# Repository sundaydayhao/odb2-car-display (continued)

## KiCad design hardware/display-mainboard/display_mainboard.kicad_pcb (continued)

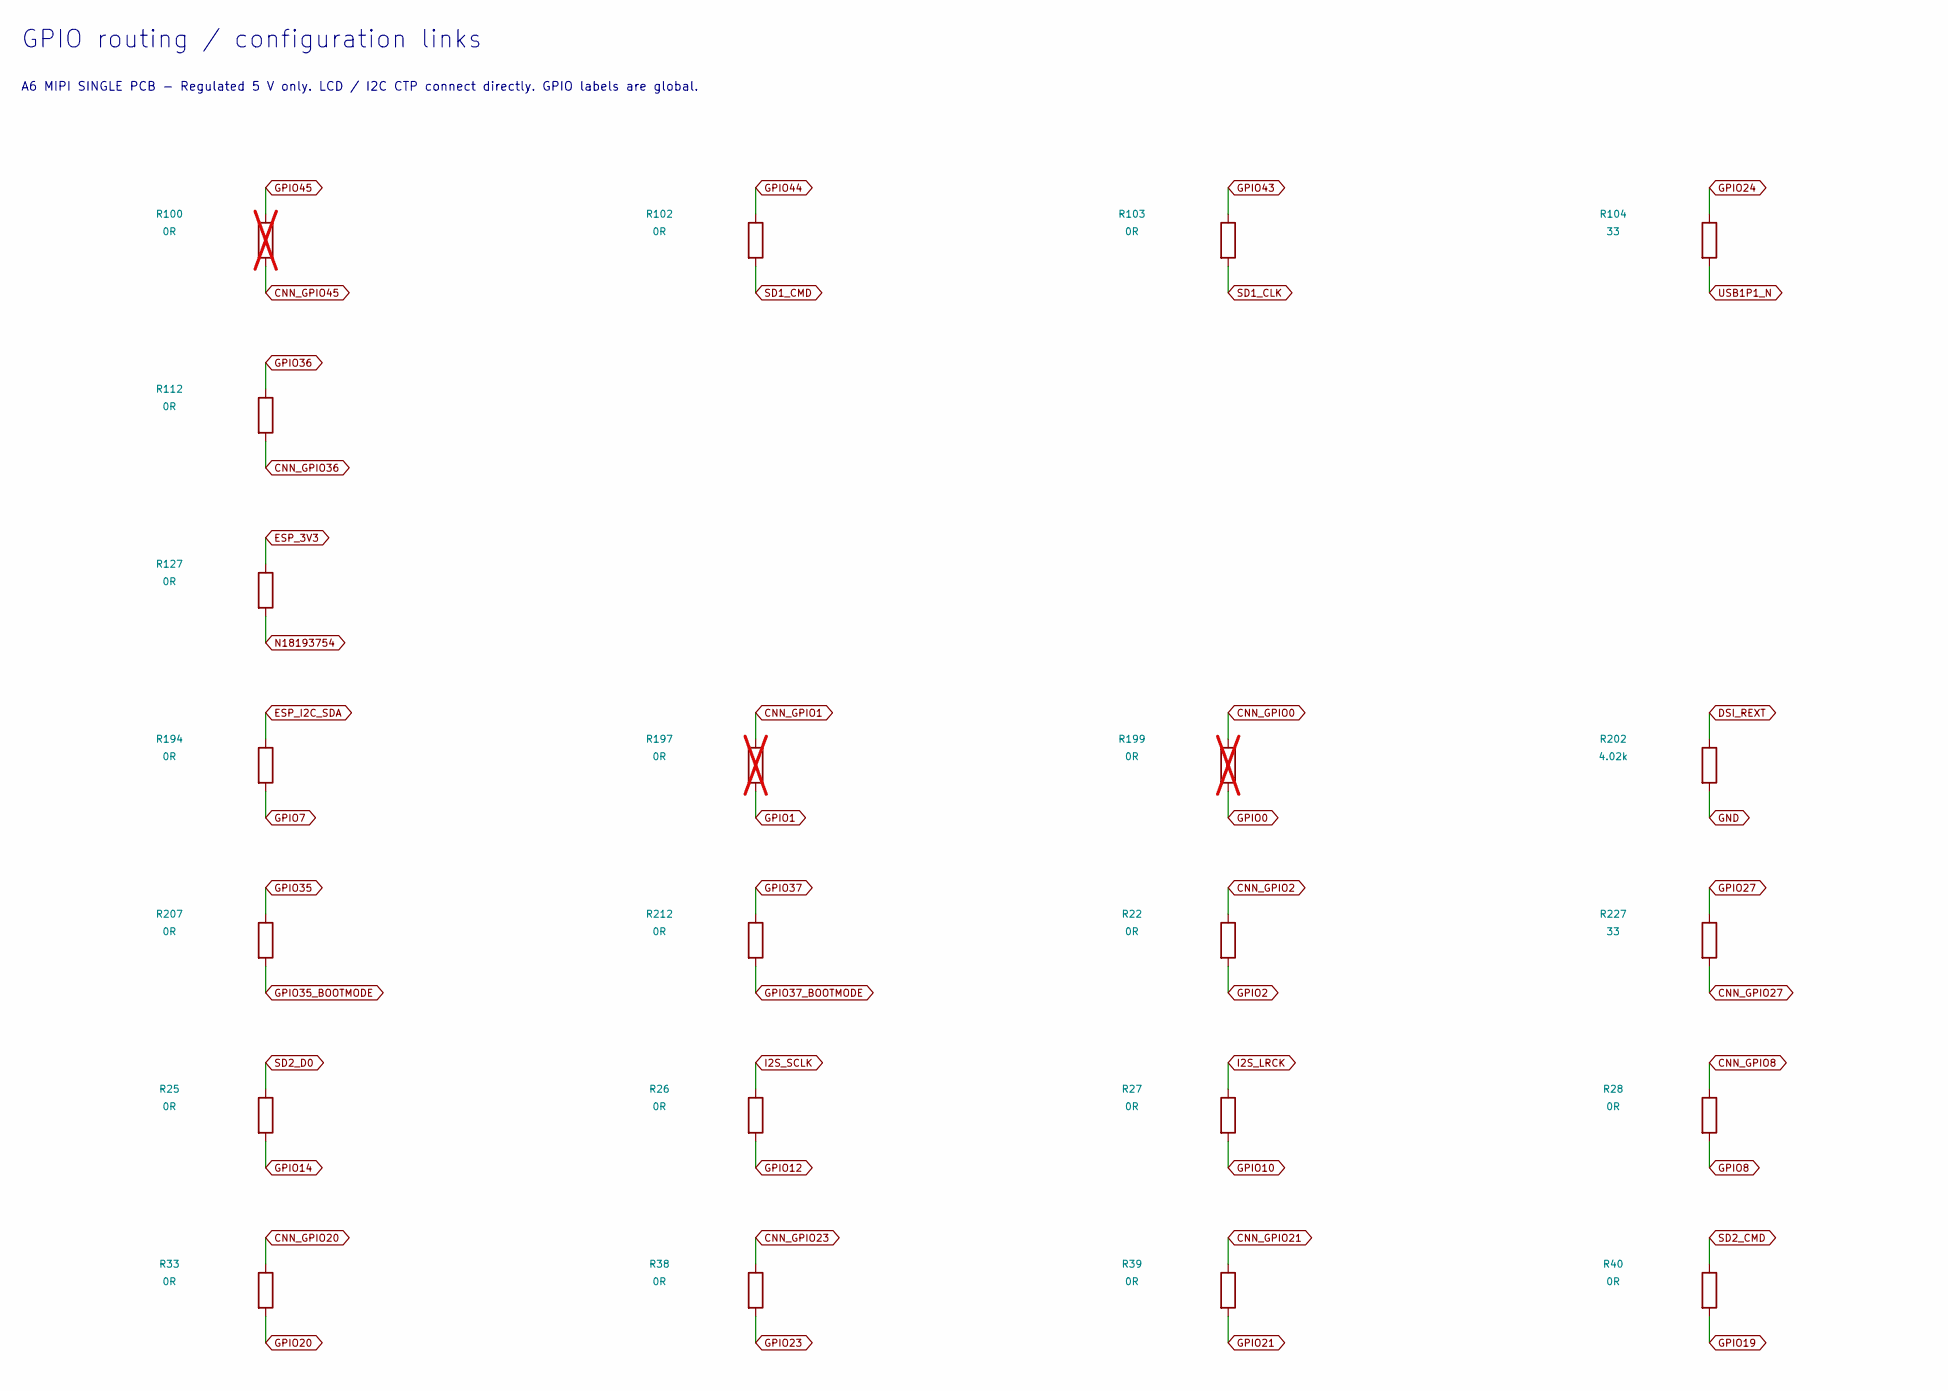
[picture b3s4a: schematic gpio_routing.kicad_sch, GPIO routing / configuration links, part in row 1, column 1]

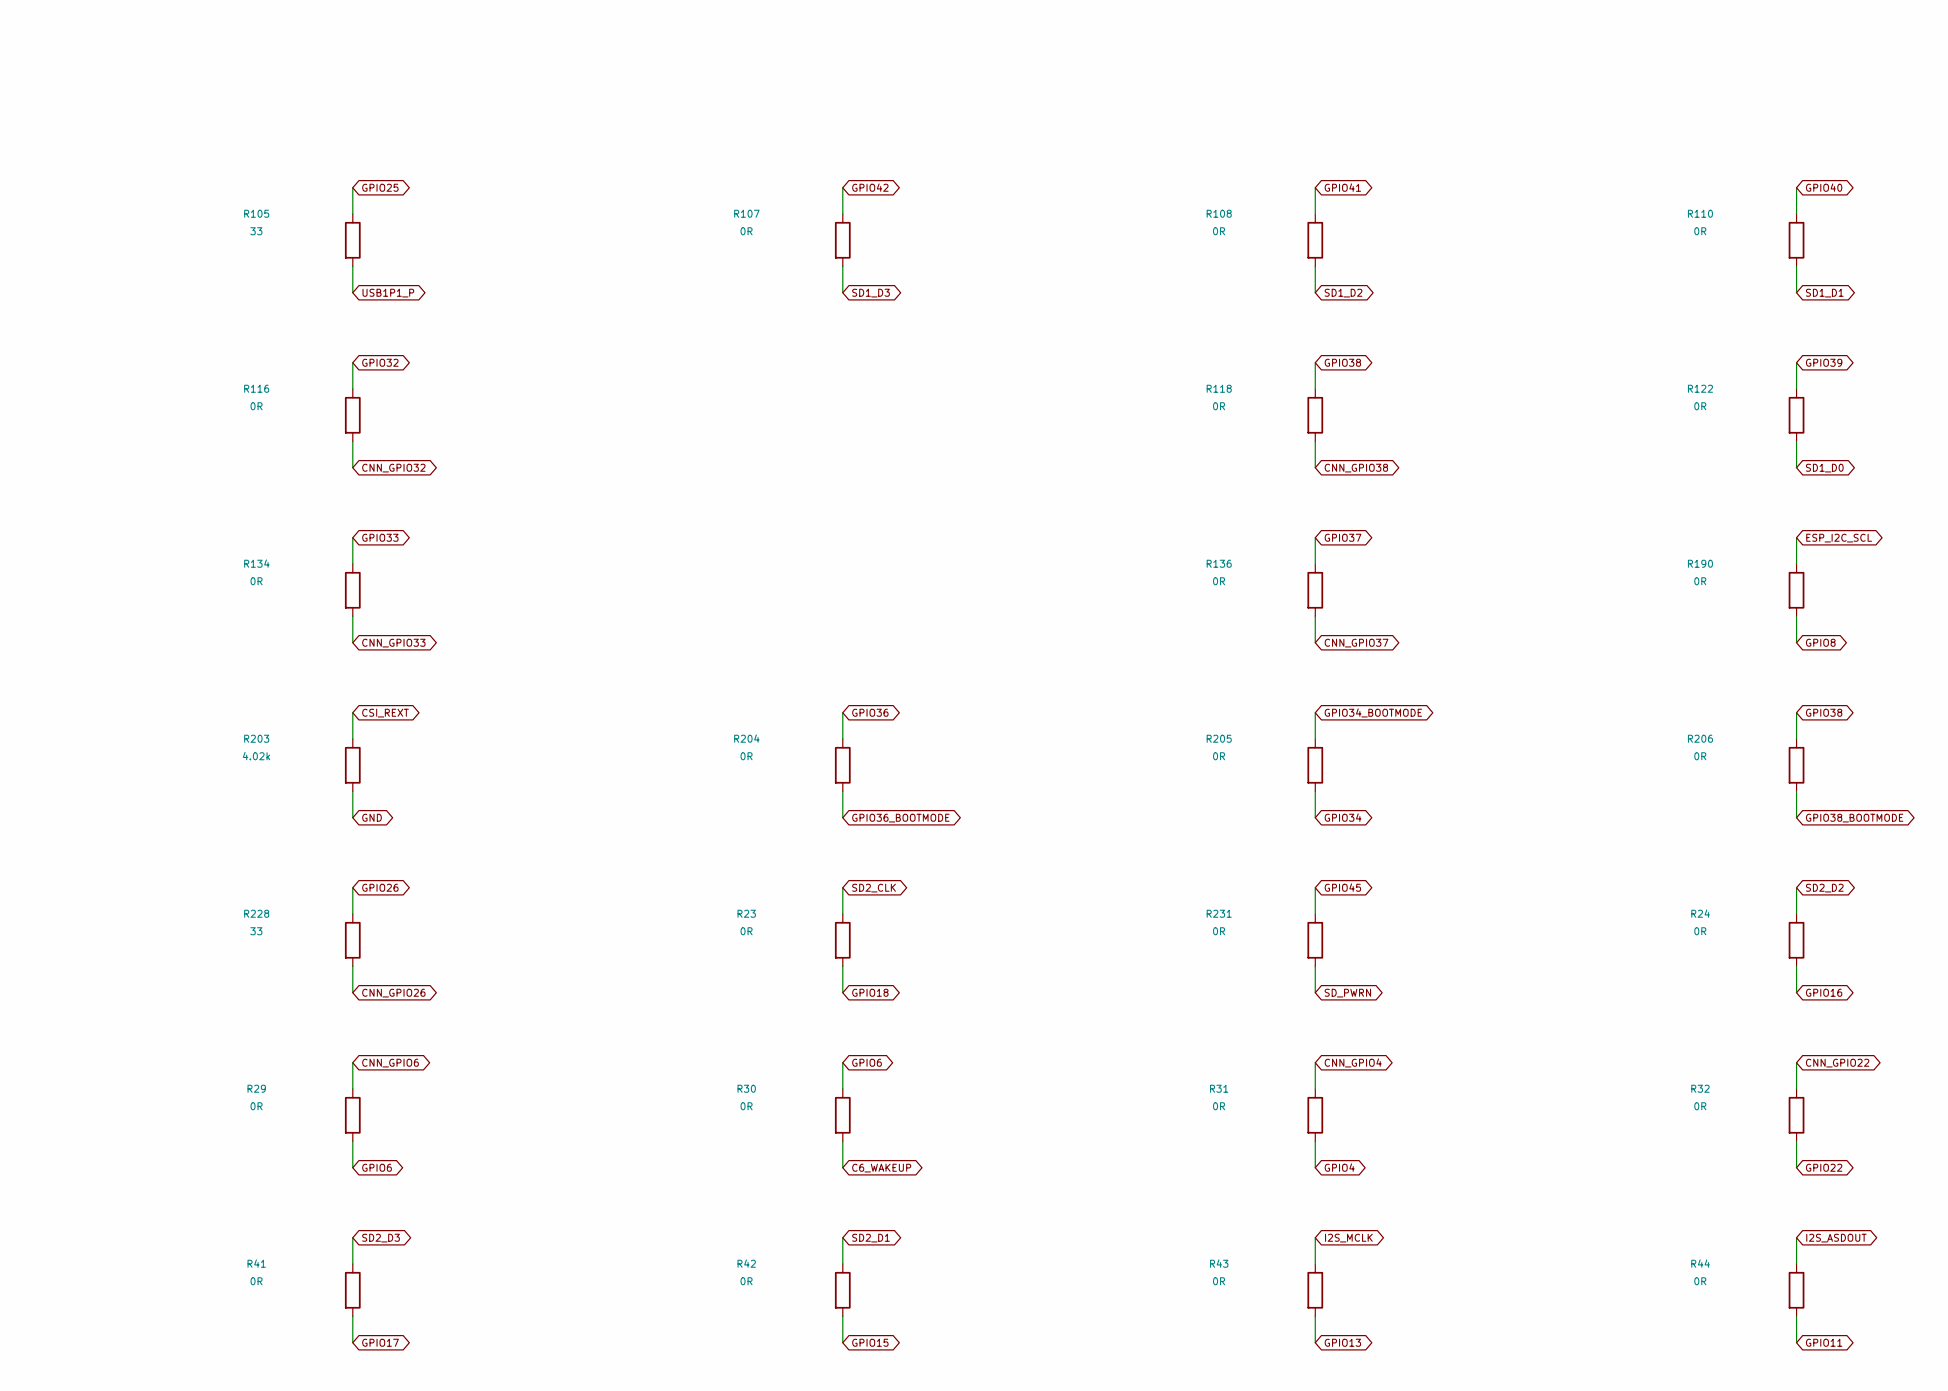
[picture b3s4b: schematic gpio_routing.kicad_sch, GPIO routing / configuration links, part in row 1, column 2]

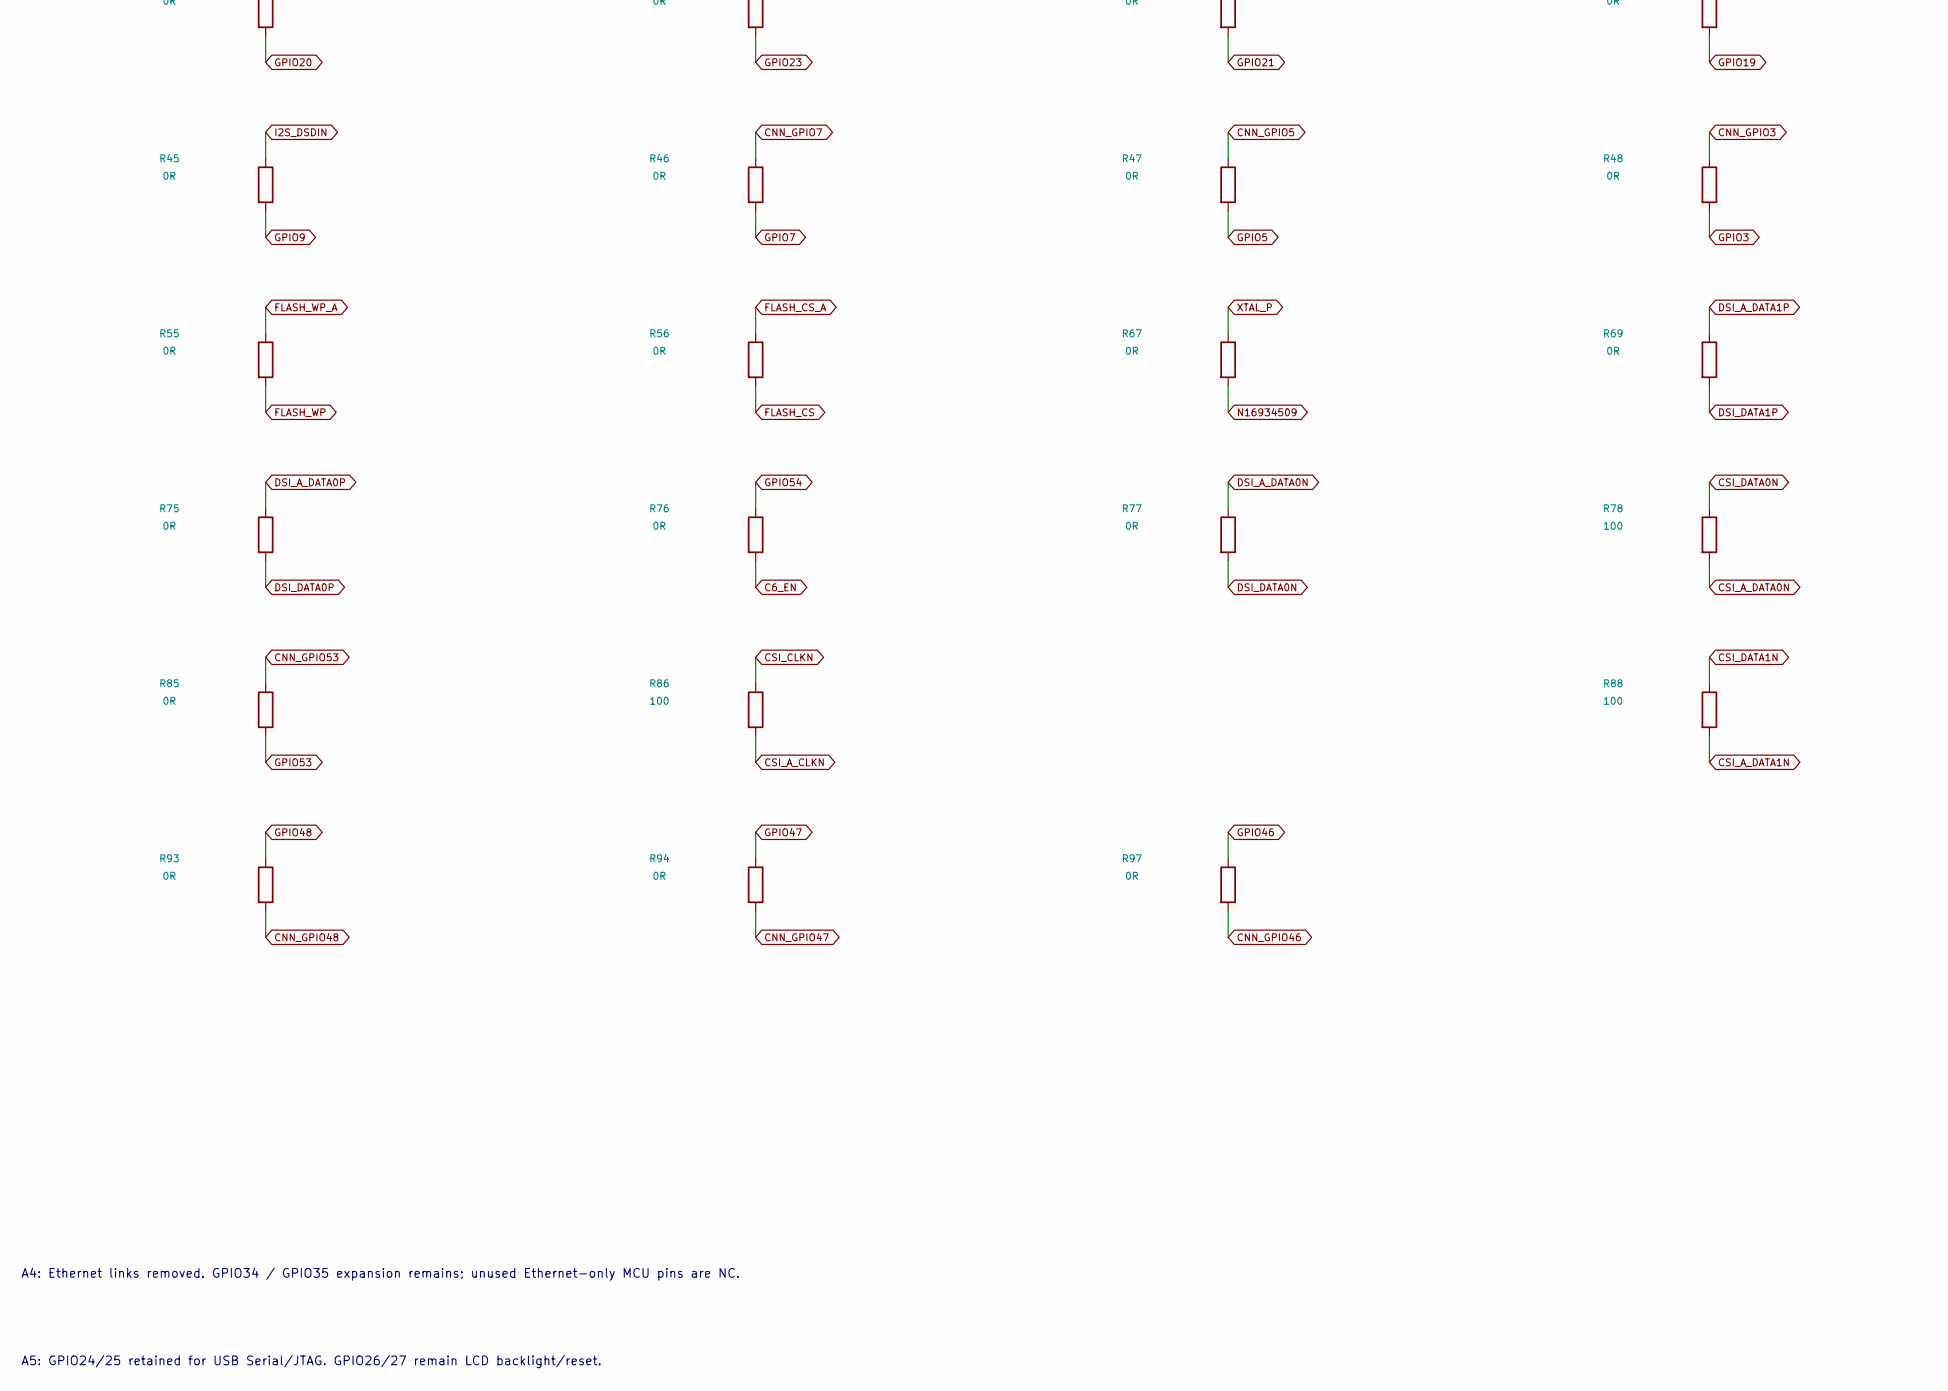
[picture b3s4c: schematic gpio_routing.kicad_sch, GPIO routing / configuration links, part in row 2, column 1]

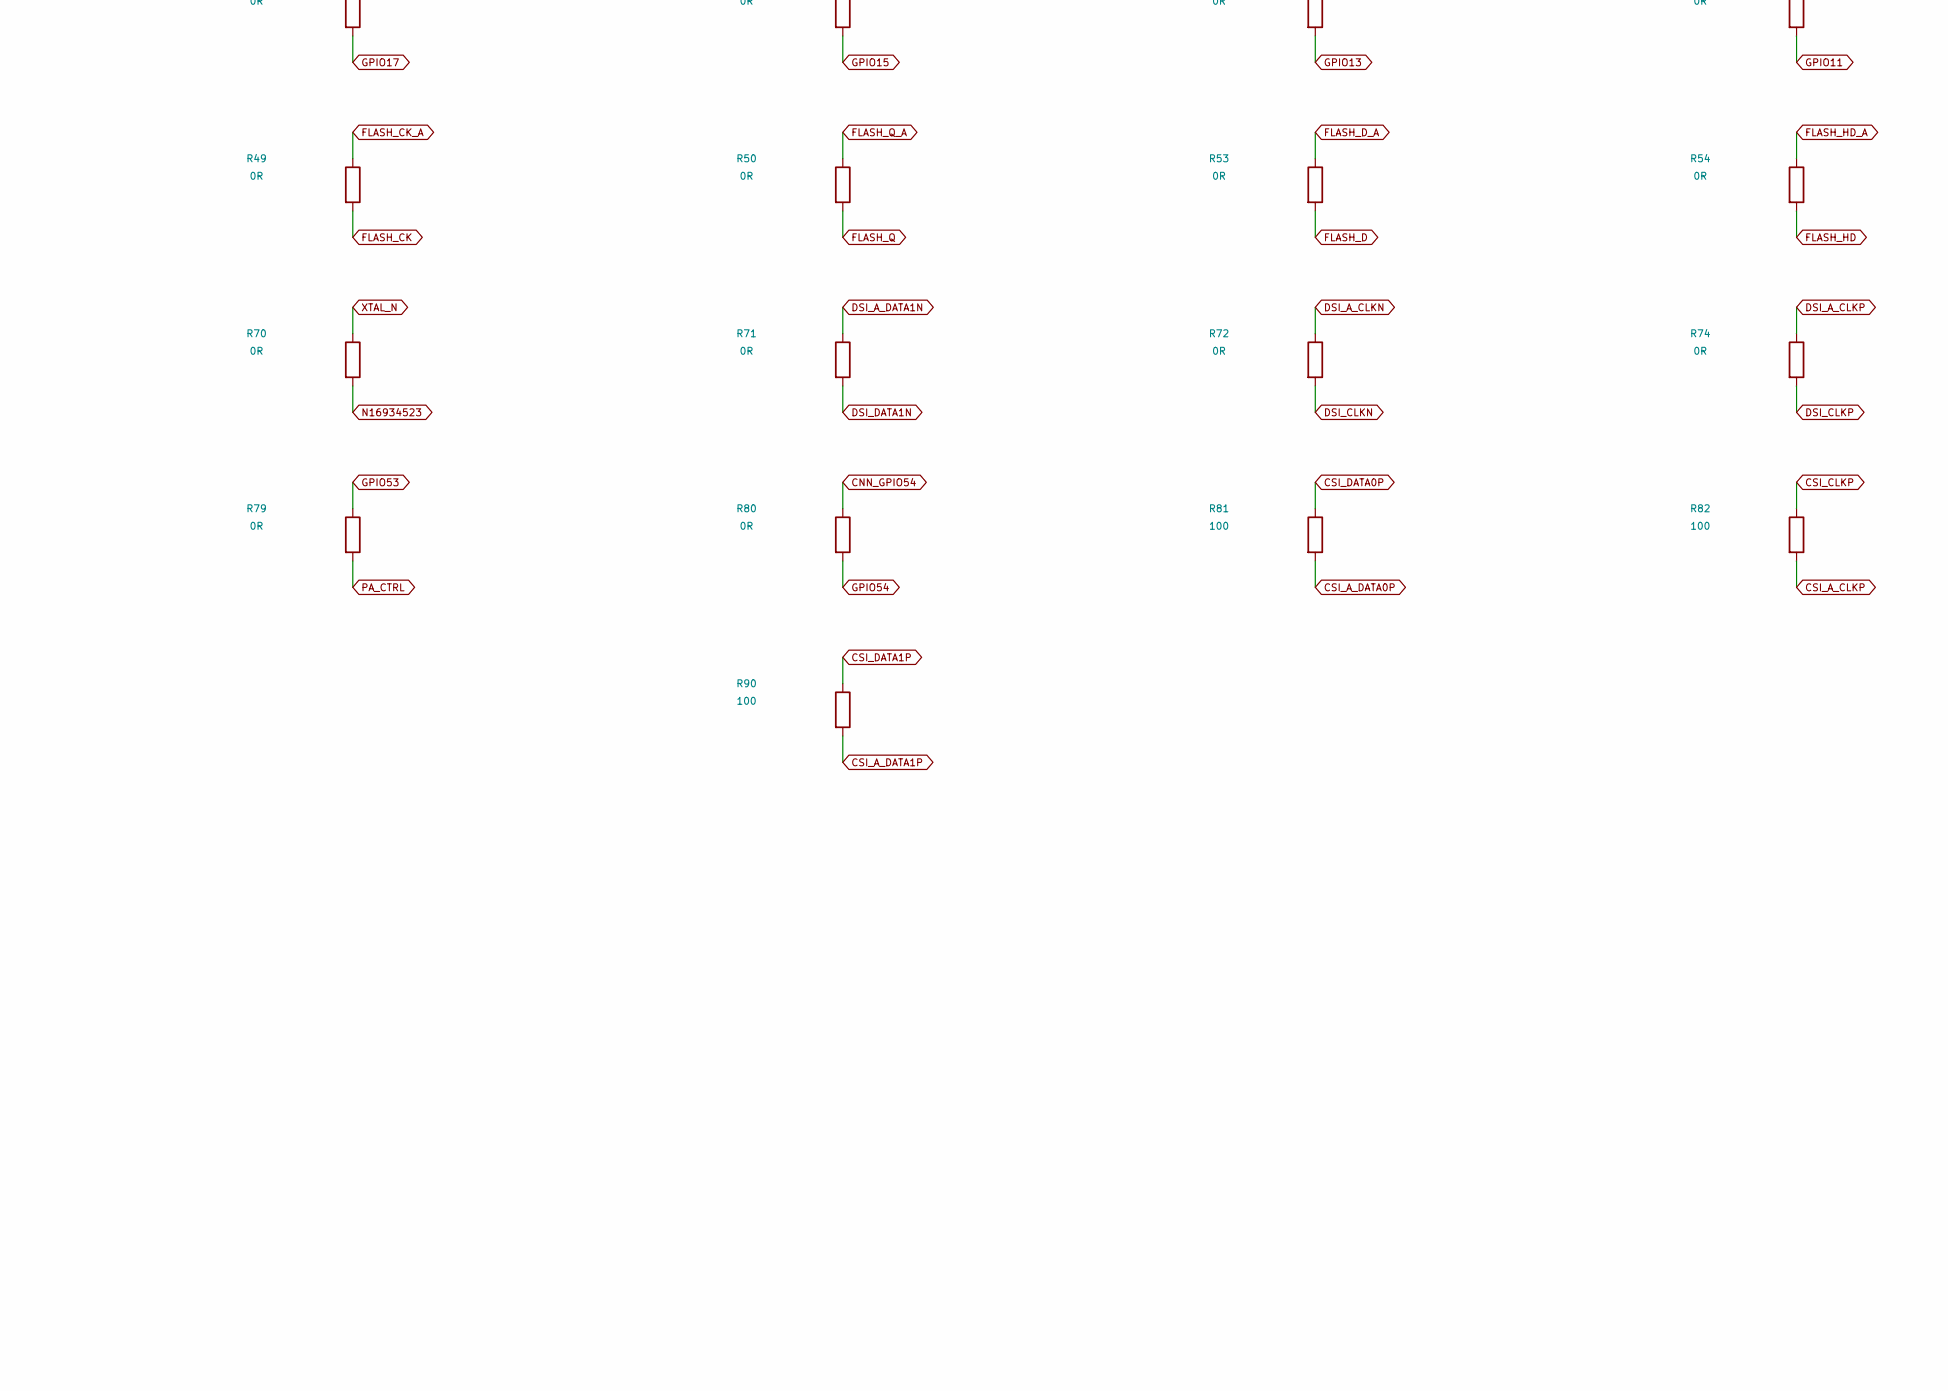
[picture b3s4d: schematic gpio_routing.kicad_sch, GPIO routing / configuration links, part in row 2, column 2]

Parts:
R22, R23, R24, R25, R26, R27, R28, R29, R30, R31, R32, R33, R38, R39, R40, R41, R42, R43, R44, R45, R46, R47, R48, R49, R50, R53, R54, R55, R56, R67, R70, R76, R79, R80, R85, R93, R94, R97, R102, R103, R107, R108, R110, R112, R116, R118, R122, R134, R136, R231: 0R; R0402__6ca295102a
R69, R71, R72, R74, R75, R77: 0R; R0201__aad23a0937
R78, R81, R82, R86, R88, R90: 100; R0201__aad23a0937
R100, R197, R199: 0R; R0402_097d4b0b__c1bfdfccc2; not fitted
R104, R105: 33; R0402__6ca295102a
R127: 0R; R0603__ca4d6f8805
R190, R194, R204, R205, R206, R207, R212: 0R; R0402_097d4b0b__c1bfdfccc2
R202, R203: 4.02k; R0402_097d4b0b__c1bfdfccc2
R227, R228: 33; R0402_097d4b0b__c1bfdfccc2

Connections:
C6_EN: R76.2; also elsewhere on the board
C6_WAKEUP: R30.2; also elsewhere on the board
CNN_GPIO0: R199.1; also elsewhere on the board
CNN_GPIO1: R197.1; also elsewhere on the board
CNN_GPIO2: R22.1; also elsewhere on the board
CNN_GPIO3: R48.1; also elsewhere on the board
CNN_GPIO4: R31.1; also elsewhere on the board
CNN_GPIO5: R47.1; also elsewhere on the board
CNN_GPIO6: R29.1; also elsewhere on the board
CNN_GPIO7: R46.1; also elsewhere on the board
CNN_GPIO8: R28.1; also elsewhere on the board
CNN_GPIO20: R33.1; also elsewhere on the board
CNN_GPIO21: R39.1; also elsewhere on the board
CNN_GPIO22: R32.1; also elsewhere on the board
CNN_GPIO23: R38.1; also elsewhere on the board
CNN_GPIO26: R228.2; also elsewhere on the board
CNN_GPIO27: R227.2; also elsewhere on the board
CNN_GPIO32: R116.2; also elsewhere on the board
CNN_GPIO33: R134.2; also elsewhere on the board
CNN_GPIO36: R112.2; also elsewhere on the board
CNN_GPIO37: R136.2; also elsewhere on the board
CNN_GPIO38: R118.2; also elsewhere on the board
CNN_GPIO45: R100.2; also elsewhere on the board
CNN_GPIO46: R97.2; also elsewhere on the board
CNN_GPIO47: R94.2; also elsewhere on the board
CNN_GPIO48: R93.2; also elsewhere on the board
CNN_GPIO53: R85.1; also elsewhere on the board
CNN_GPIO54: R80.1; also elsewhere on the board
CSI_A_CLKN: R86.2; also elsewhere on the board
CSI_A_CLKP: R82.2; also elsewhere on the board
CSI_A_DATA0N: R78.2; also elsewhere on the board
CSI_A_DATA0P: R81.2; also elsewhere on the board
CSI_A_DATA1N: R88.2; also elsewhere on the board
CSI_A_DATA1P: R90.2; also elsewhere on the board
CSI_CLKN: R86.1; also elsewhere on the board
CSI_CLKP: R82.1; also elsewhere on the board
CSI_DATA0N: R78.1; also elsewhere on the board
CSI_DATA0P: R81.1; also elsewhere on the board
CSI_DATA1N: R88.1; also elsewhere on the board
CSI_DATA1P: R90.1; also elsewhere on the board
CSI_REXT: R203.1; also elsewhere on the board
DSI_A_CLKN: R72.1; also elsewhere on the board
DSI_A_CLKP: R74.1; also elsewhere on the board
DSI_A_DATA0N: R77.1; also elsewhere on the board
DSI_A_DATA0P: R75.1; also elsewhere on the board
DSI_A_DATA1N: R71.1; also elsewhere on the board
DSI_A_DATA1P: R69.1; also elsewhere on the board
DSI_CLKN: R72.2; also elsewhere on the board
DSI_CLKP: R74.2; also elsewhere on the board
DSI_DATA0N: R77.2; also elsewhere on the board
DSI_DATA0P: R75.2; also elsewhere on the board
DSI_DATA1N: R71.2; also elsewhere on the board
DSI_DATA1P: R69.2; also elsewhere on the board
DSI_REXT: R202.1; also elsewhere on the board
ESP_3V3: R127.1; also elsewhere on the board
ESP_I2C_SCL: R190.1; also elsewhere on the board
ESP_I2C_SDA: R194.1; also elsewhere on the board
FLASH_CK: R49.2; also elsewhere on the board
FLASH_CK_A: R49.1; also elsewhere on the board
FLASH_CS: R56.2; also elsewhere on the board
FLASH_CS_A: R56.1; also elsewhere on the board
FLASH_D: R53.2; also elsewhere on the board
FLASH_D_A: R53.1; also elsewhere on the board
FLASH_HD: R54.2; also elsewhere on the board
FLASH_HD_A: R54.1; also elsewhere on the board
FLASH_Q: R50.2; also elsewhere on the board
FLASH_Q_A: R50.1; also elsewhere on the board
FLASH_WP: R55.2; also elsewhere on the board
FLASH_WP_A: R55.1; also elsewhere on the board
GPIO0: R199.2; also elsewhere on the board
GPIO1: R197.2; also elsewhere on the board
GPIO2: R22.2; also elsewhere on the board
GPIO3: R48.2; also elsewhere on the board
GPIO4: R31.2; also elsewhere on the board
GPIO5: R47.2; also elsewhere on the board
GPIO6: R29.2, R30.1; also elsewhere on the board
GPIO7: R46.2, R194.2; also elsewhere on the board
GPIO8: R28.2, R190.2; also elsewhere on the board
GPIO9: R45.2; also elsewhere on the board
GPIO10: R27.2; also elsewhere on the board
GPIO11: R44.2; also elsewhere on the board
GPIO12: R26.2; also elsewhere on the board
GPIO13: R43.2; also elsewhere on the board
GPIO14: R25.2; also elsewhere on the board
GPIO15: R42.2; also elsewhere on the board
GPIO16: R24.2; also elsewhere on the board
GPIO17: R41.2; also elsewhere on the board
GPIO18: R23.2; also elsewhere on the board
GPIO19: R40.2; also elsewhere on the board
GPIO20: R33.2; also elsewhere on the board
GPIO21: R39.2; also elsewhere on the board
GPIO22: R32.2; also elsewhere on the board
GPIO23: R38.2; also elsewhere on the board
GPIO24: R104.1; also elsewhere on the board
GPIO25: R105.1; also elsewhere on the board
GPIO26: R228.1; also elsewhere on the board
GPIO27: R227.1; also elsewhere on the board
GPIO32: R116.1; also elsewhere on the board
GPIO33: R134.1; also elsewhere on the board
GPIO34: R205.2; also elsewhere on the board
GPIO34_BOOTMODE: R205.1; also elsewhere on the board
GPIO35: R207.1; also elsewhere on the board
GPIO35_BOOTMODE: R207.2; also elsewhere on the board
GPIO36: R112.1, R204.1; also elsewhere on the board
GPIO36_BOOTMODE: R204.2; also elsewhere on the board
GPIO37: R136.1, R212.1; also elsewhere on the board
GPIO37_BOOTMODE: R212.2; also elsewhere on the board
GPIO38: R118.1, R206.1; also elsewhere on the board
GPIO38_BOOTMODE: R206.2; also elsewhere on the board
GPIO39: R122.1; also elsewhere on the board
GPIO40: R110.1; also elsewhere on the board
GPIO41: R108.1; also elsewhere on the board
GPIO42: R107.1; also elsewhere on the board
GPIO43: R103.1; also elsewhere on the board
GPIO44: R102.1; also elsewhere on the board
GPIO45: R100.1, R231.1; also elsewhere on the board
GPIO46: R97.1; also elsewhere on the board
GPIO47: R94.1; also elsewhere on the board
GPIO48: R93.1; also elsewhere on the board
GPIO53: R79.1, R85.2; also elsewhere on the board
GPIO54: R76.1, R80.2; also elsewhere on the board
I2S_ASDOUT: R44.1; also elsewhere on the board
I2S_DSDIN: R45.1; also elsewhere on the board
I2S_LRCK: R27.1; also elsewhere on the board
I2S_MCLK: R43.1; also elsewhere on the board
I2S_SCLK: R26.1; also elsewhere on the board
N16934509: R67.2; also elsewhere on the board
N16934523: R70.2; also elsewhere on the board
N18193754: R127.2; also elsewhere on the board
PA_CTRL: R79.2; also elsewhere on the board
SD1_CLK: R103.2; also elsewhere on the board
SD1_CMD: R102.2; also elsewhere on the board
SD1_D0: R122.2; also elsewhere on the board
SD1_D1: R110.2; also elsewhere on the board
SD1_D2: R108.2; also elsewhere on the board
SD1_D3: R107.2; also elsewhere on the board
SD2_CLK: R23.1; also elsewhere on the board
SD2_CMD: R40.1; also elsewhere on the board
SD2_D0: R25.1; also elsewhere on the board
SD2_D1: R42.1; also elsewhere on the board
SD2_D2: R24.1; also elsewhere on the board
SD2_D3: R41.1; also elsewhere on the board
SD_PWRN: R231.2; also elsewhere on the board
USB1P1_N: R104.2; also elsewhere on the board
USB1P1_P: R105.2; also elsewhere on the board
XTAL_N: R70.1; also elsewhere on the board
XTAL_P: R67.1; also elsewhere on the board

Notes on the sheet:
GPIO routing / configuration links
A6 MIPI SINGLE PCB - Regulated 5 V only. LCD / I2C CTP connect directly. GPIO labels are global.
A4: Ethernet links removed. GPIO34 / GPIO35 expansion remains; unused Ethernet-only MCU pins are NC.
A5: GPIO24/25 retained for USB Serial/JTAG. GPIO26/27 remain LCD backlight/reset.

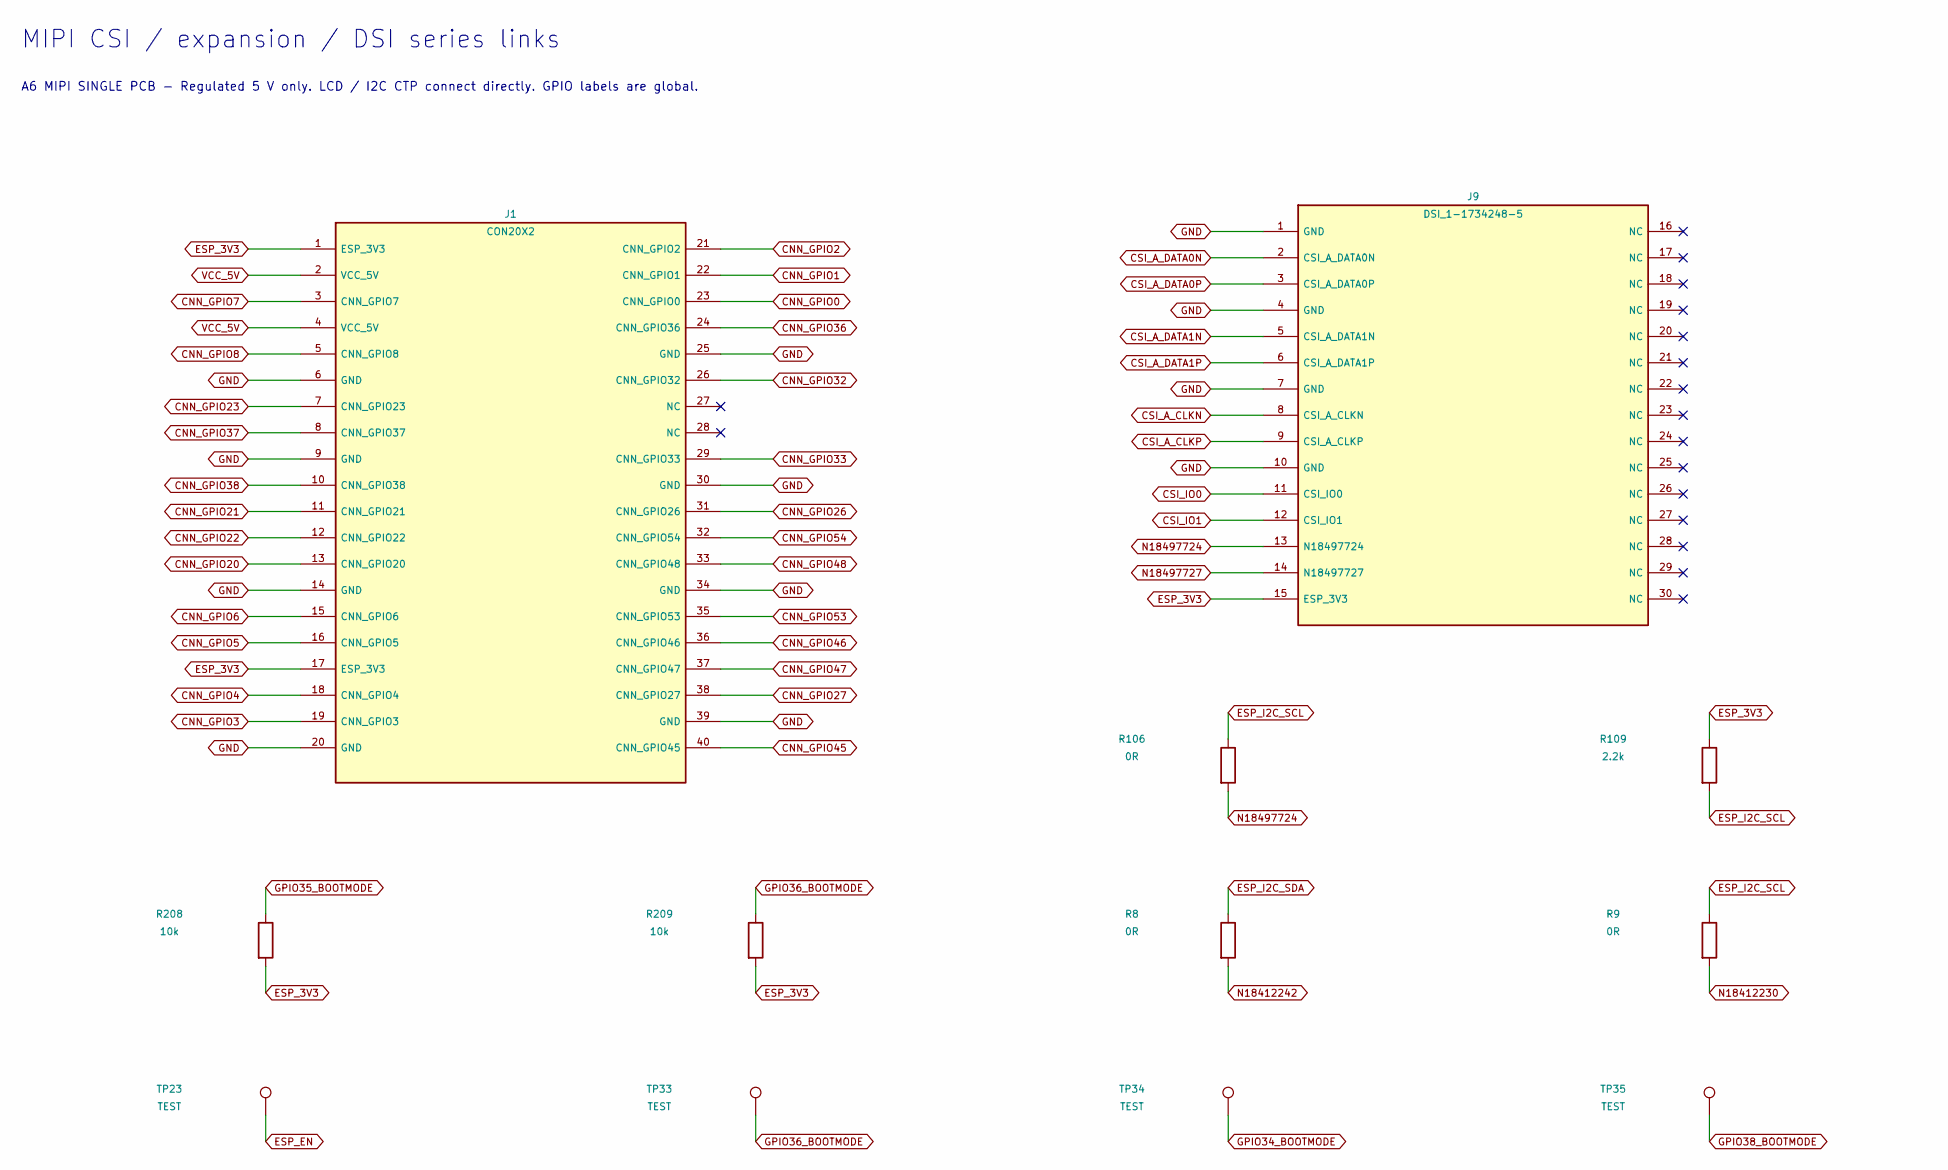
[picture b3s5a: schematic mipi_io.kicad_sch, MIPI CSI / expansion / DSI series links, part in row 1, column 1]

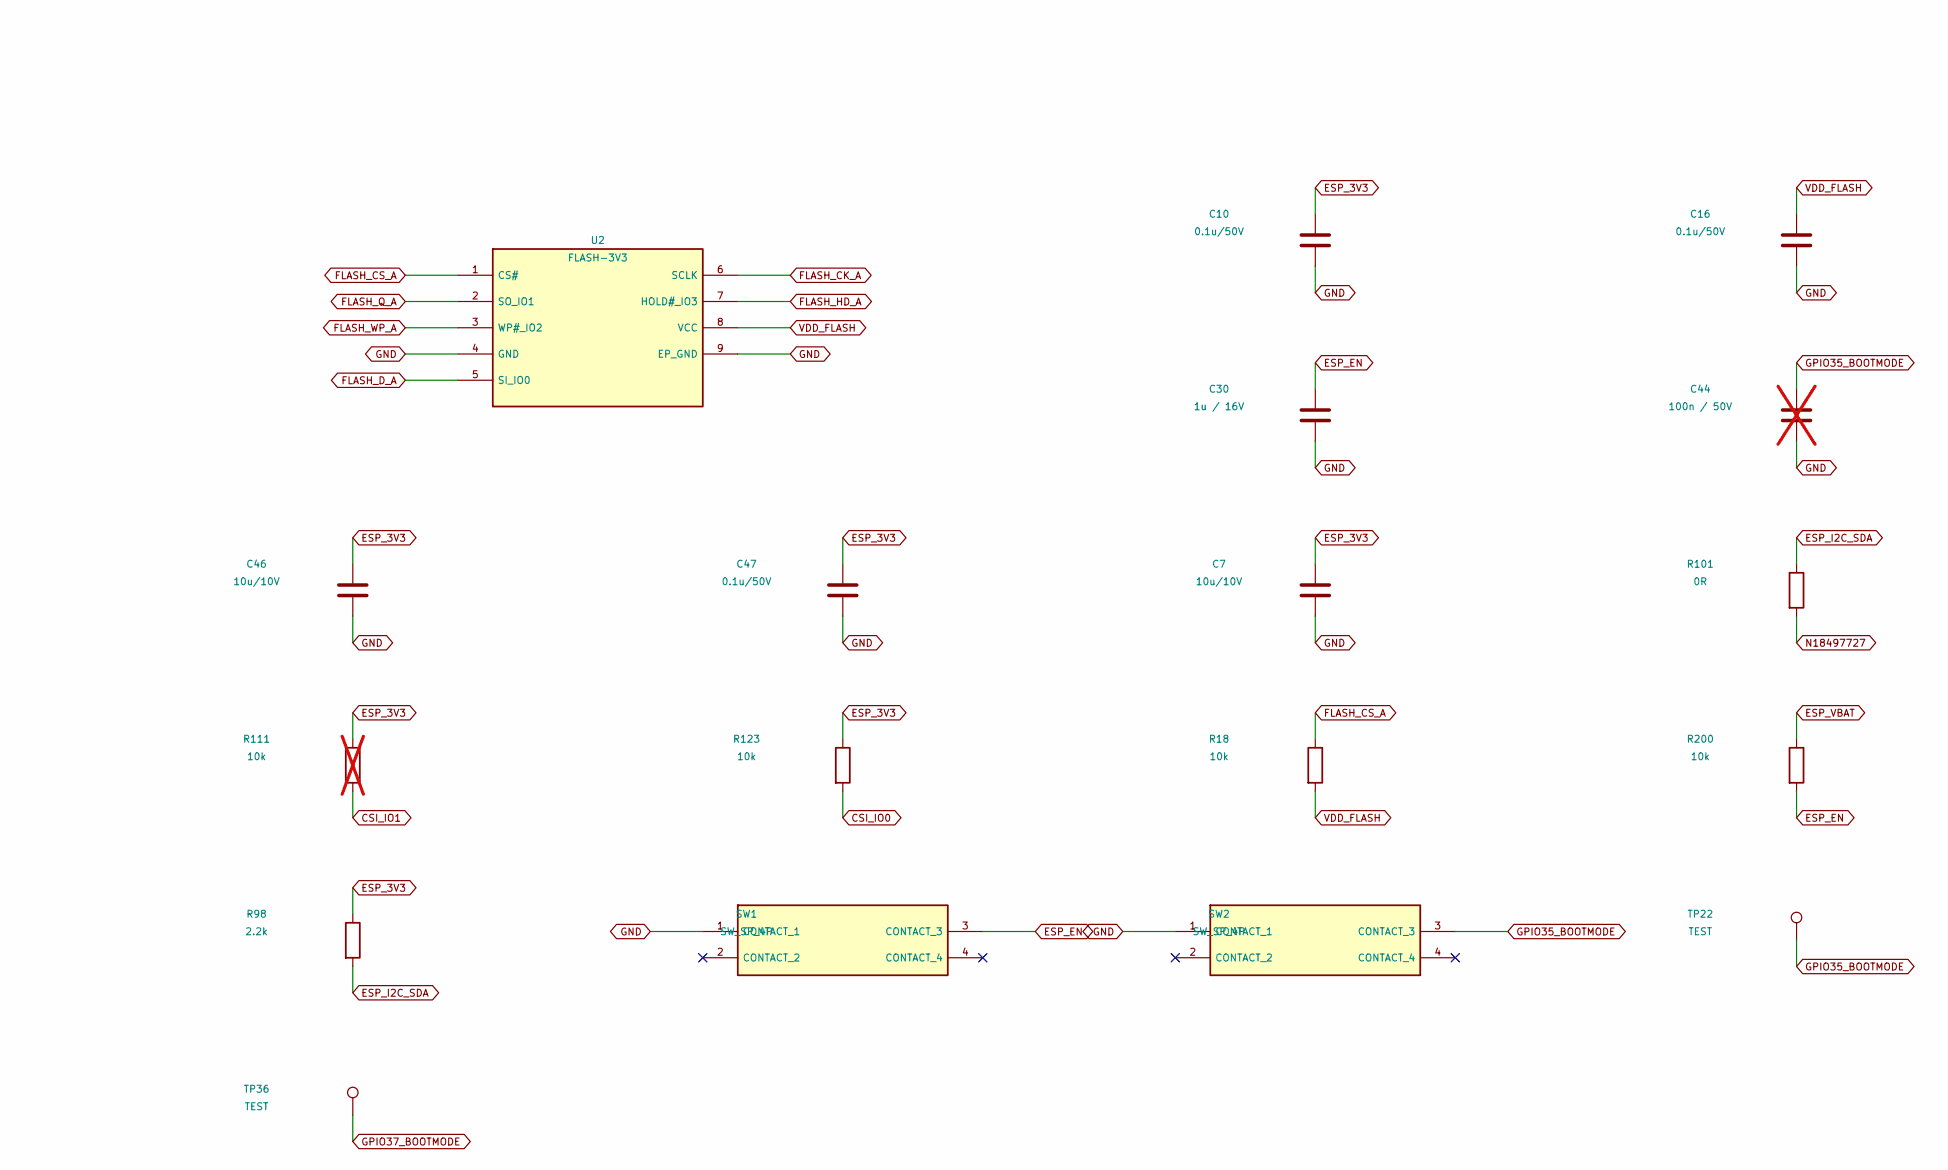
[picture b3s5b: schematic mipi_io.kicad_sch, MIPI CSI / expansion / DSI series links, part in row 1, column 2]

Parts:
C7: 10u/10V; C0603__1e7c8298a8
C10, C16: 0.1u/50V; C0402__df1ad35910
C30: 1u / 16V; C0402__df1ad35910
C44: 100n / 50V; C0402__df1ad35910; not fitted
C46: 10u/10V; C0603_1ead970f__4ff9dc89d7
C47: 0.1u/50V; C0402_097d4b0b__328ab4e626
J1: CON20X2; CON20X2_2P54__b2870a8640
J9: DSI_1-1734248-5; FFC_15P_1_MIPI__e4ede50f2f; MPN 1.0K-GT-15PB
R8, R9: 0R; R0402__6ca295102a
R18: 10k; R0402__6ca295102a
R98, R109: 2.2k; R0402_097d4b0b__c1bfdfccc2
R101, R106: 0R; R0402_097d4b0b__c1bfdfccc2
R111: 10k; R0402_097d4b0b__c1bfdfccc2; not fitted
R123, R200, R208, R209: 10k; R0402_097d4b0b__c1bfdfccc2
SW1, SW2: SW_SP_4P; SW4-4P5X4P5X2P9-SMT__a0ea52c7f0; MPN K2-1109SP-B4SA-01
TP22, TP23: TEST; TPC1__56d55e75a0
TP33, TP34, TP35, TP36: TEST; TPC1_fd69f0aa__930cba657a
U2: FLASH-3V3; WSON6X8__20e6c1659c; MPN GD25Q128ESIG

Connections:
CNN_GPIO0: J1.23 (CNN_GPIO0); also elsewhere on the board
CNN_GPIO1: J1.22 (CNN_GPIO1); also elsewhere on the board
CNN_GPIO2: J1.21 (CNN_GPIO2); also elsewhere on the board
CNN_GPIO3: J1.19 (CNN_GPIO3); also elsewhere on the board
CNN_GPIO4: J1.18 (CNN_GPIO4); also elsewhere on the board
CNN_GPIO5: J1.16 (CNN_GPIO5); also elsewhere on the board
CNN_GPIO6: J1.15 (CNN_GPIO6); also elsewhere on the board
CNN_GPIO7: J1.3 (CNN_GPIO7); also elsewhere on the board
CNN_GPIO8: J1.5 (CNN_GPIO8); also elsewhere on the board
CNN_GPIO20: J1.13 (CNN_GPIO20); also elsewhere on the board
CNN_GPIO21: J1.11 (CNN_GPIO21); also elsewhere on the board
CNN_GPIO22: J1.12 (CNN_GPIO22); also elsewhere on the board
CNN_GPIO23: J1.7 (CNN_GPIO23); also elsewhere on the board
CNN_GPIO26: J1.31 (CNN_GPIO26); also elsewhere on the board
CNN_GPIO27: J1.38 (CNN_GPIO27); also elsewhere on the board
CNN_GPIO32: J1.26 (CNN_GPIO32); also elsewhere on the board
CNN_GPIO33: J1.29 (CNN_GPIO33); also elsewhere on the board
CNN_GPIO36: J1.24 (CNN_GPIO36); also elsewhere on the board
CNN_GPIO37: J1.8 (CNN_GPIO37); also elsewhere on the board
CNN_GPIO38: J1.10 (CNN_GPIO38); also elsewhere on the board
CNN_GPIO45: J1.40 (CNN_GPIO45); also elsewhere on the board
CNN_GPIO46: J1.36 (CNN_GPIO46); also elsewhere on the board
CNN_GPIO47: J1.37 (CNN_GPIO47); also elsewhere on the board
CNN_GPIO48: J1.33 (CNN_GPIO48); also elsewhere on the board
CNN_GPIO53: J1.35 (CNN_GPIO53); also elsewhere on the board
CNN_GPIO54: J1.32 (CNN_GPIO54); also elsewhere on the board
CSI_A_CLKN: J9.8 (CSI_A_CLKN); also elsewhere on the board
CSI_A_CLKP: J9.9 (CSI_A_CLKP); also elsewhere on the board
CSI_A_DATA0N: J9.2 (CSI_A_DATA0N); also elsewhere on the board
CSI_A_DATA0P: J9.3 (CSI_A_DATA0P); also elsewhere on the board
CSI_A_DATA1N: J9.5 (CSI_A_DATA1N); also elsewhere on the board
CSI_A_DATA1P: J9.6 (CSI_A_DATA1P); also elsewhere on the board
CSI_IO0: J9.11 (CSI_IO0), R123.2
CSI_IO1: J9.12 (CSI_IO1), R111.2
ESP_3V3: C7.1, C10.1, C46.1, C47.1, J1.1 (ESP_3V3), J1.17 (ESP_3V3), J9.15 (ESP_3V3), R98.1, R109.1, R111.1, R123.1, R208.2, R209.2; also elsewhere on the board
ESP_EN: C30.1, R200.2, SW1.3 (CONTACT_3), TP23.1; also elsewhere on the board
ESP_I2C_SCL: R9.1, R106.1, R109.2; also elsewhere on the board
ESP_I2C_SDA: R8.1, R98.2, R101.1; also elsewhere on the board
ESP_VBAT: R200.1; also elsewhere on the board
FLASH_CK_A: U2.6 (SCLK); also elsewhere on the board
FLASH_CS_A: R18.1, U2.1 (CS#); also elsewhere on the board
FLASH_D_A: U2.5 (SI_IO0); also elsewhere on the board
FLASH_HD_A: U2.7 (HOLD#_IO3); also elsewhere on the board
FLASH_Q_A: U2.2 (SO_IO1); also elsewhere on the board
FLASH_WP_A: U2.3 (WP#_IO2); also elsewhere on the board
GPIO34_BOOTMODE: TP34.1; also elsewhere on the board
GPIO35_BOOTMODE: C44.1, R208.1, SW2.3 (CONTACT_3), TP22.1; also elsewhere on the board
GPIO36_BOOTMODE: R209.1, TP33.1; also elsewhere on the board
GPIO37_BOOTMODE: TP36.1; also elsewhere on the board
GPIO38_BOOTMODE: TP35.1; also elsewhere on the board
N18412230: R9.2; also elsewhere on the board
N18412242: R8.2; also elsewhere on the board
N18497724: J9.13 (N18497724), R106.2
N18497727: J9.14 (N18497727), R101.2
VCC_5V: J1.2 (VCC_5V), J1.4 (VCC_5V); also elsewhere on the board
VDD_FLASH: C16.1, R18.2, U2.8 (VCC); also elsewhere on the board

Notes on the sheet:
MIPI CSI / expansion / DSI series links
A6 MIPI SINGLE PCB - Regulated 5 V only. LCD / I2C CTP connect directly. GPIO labels are global.
